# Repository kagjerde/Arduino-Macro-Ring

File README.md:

# Arduino-Macro-Ring

This project is for a RGB LED ring for macro photography or microscopes, to reduce shadows and reflections in the image.

The LED’s are controlled by a rotary switch that selects between different modes of brightness, colour and number of LED’s lit.  
Modes:

0. Set brightness, default full brightness with white light
1. Set Colour
- White
- Warm white
- Cool white
- Blue
- Red
- Green
- Random
2. Set number of LED's
3. Rotate number of LED's
4. Two opposite LED's
5. Four opposite LED's

## Hardware

- The project contains 3D model for a small enclosure for the electronics, and an arm intended for mounting on a microscope.
- It uses a WS2812B Module Strip from [Aliexpress](https://www.aliexpress.com/item/WS2812B-Module-Strip-24-Bits-24-X-WS2812-5050-RGB-LED-Ring-Lamp-Light-with-Integrated/32842513885.html?spm=a2g0s.9042311.0.0.27424c4dtHlEIW)
- The LED strip is controlled using a Arduino Nano microcontroller. 
- The mode selection is shown on a 7-segment display.

## Software

The software is written in C and relies on the Adafruit NeoPixel library.
New modes of operation can easily be added to the program.

## Circuit diagram

## Licence

2019 MIT

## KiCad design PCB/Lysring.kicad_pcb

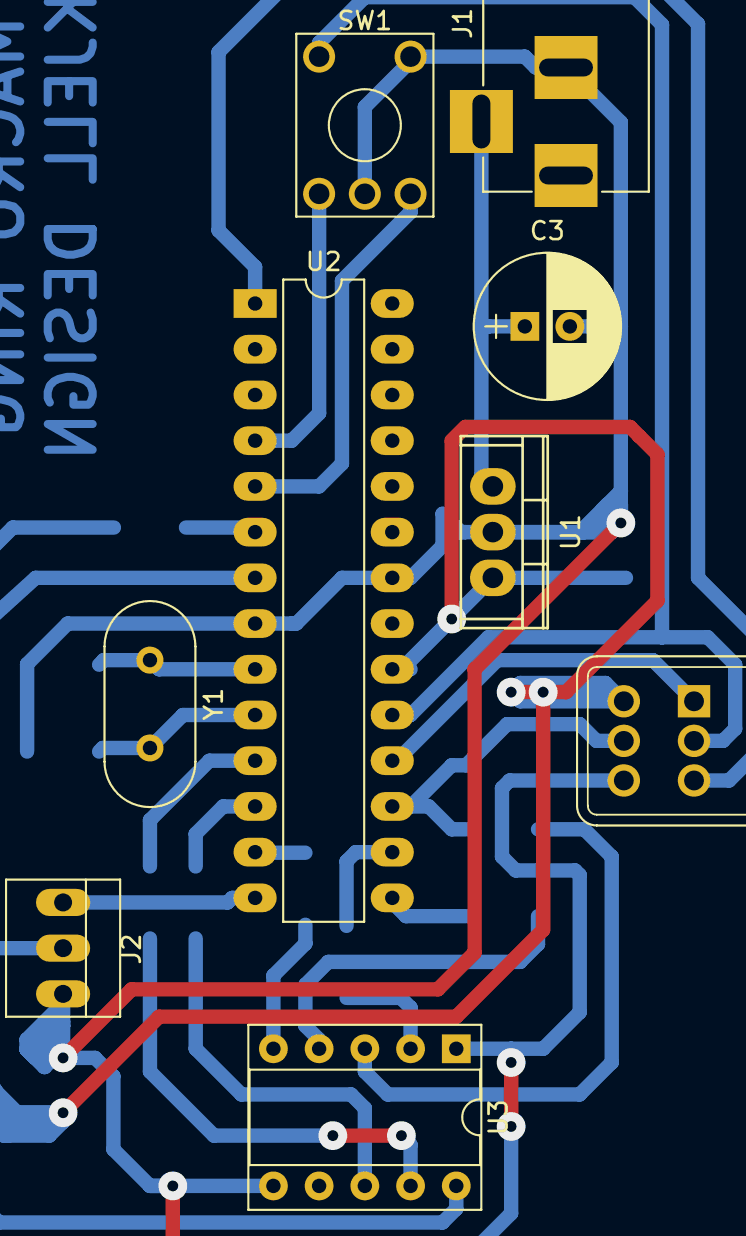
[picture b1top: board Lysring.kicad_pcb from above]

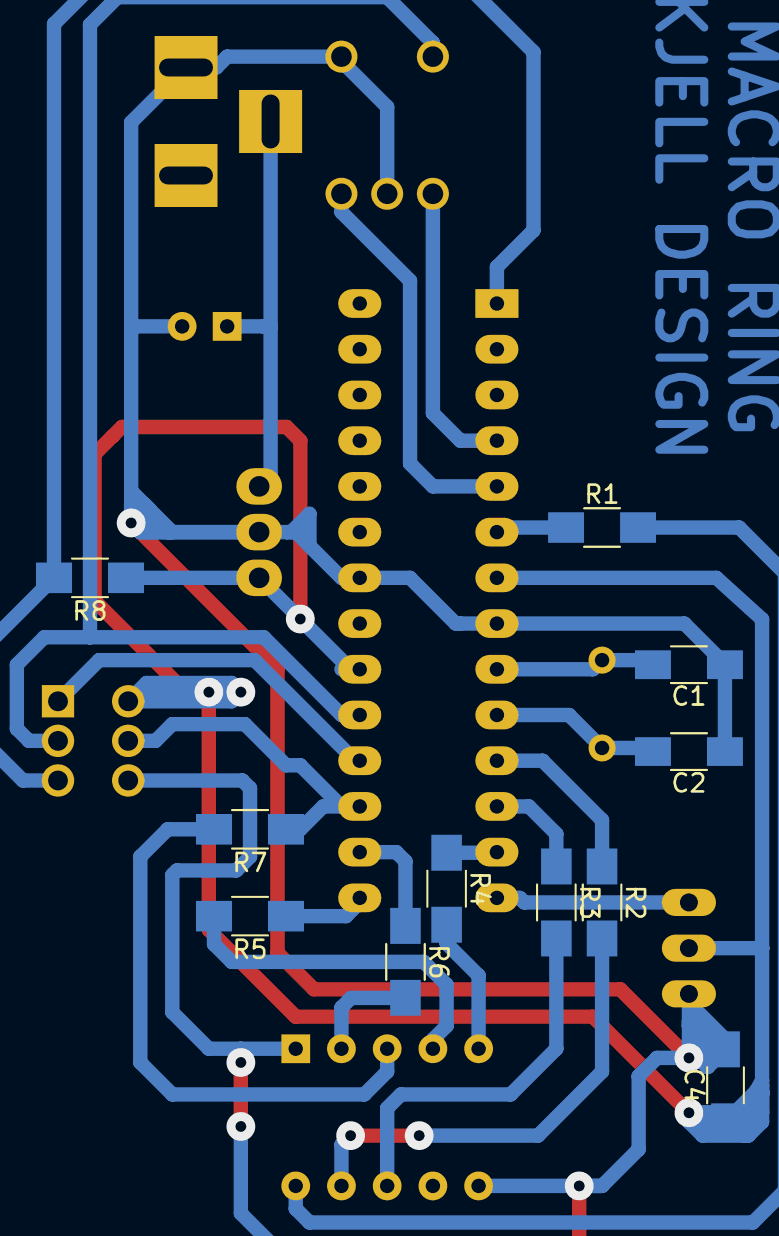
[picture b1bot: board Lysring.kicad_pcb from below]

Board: 2 copper layers, 20 parts (11 on the bottom side), 25 nets.

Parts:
C1, C2: C_Small; C_1206_HandSoldering
C3: CP; CP_Radial_D8.0mm_P2.50mm
C4: C; C_1206_HandSoldering
J1: Barrel_Jack; BARREL_JACK
J2: Conn_01x03; PINHEAD1-3
J3: Conn_02x03_Odd_Even; B06-J11DK_2x03_Pitch2.54mm
R1, R2, R3, R4, R5, R6, R7, R8: R; R_1206_HandSoldering
SW1: Rotary_Encoder_Switch; KSA_Tactile_SPST
U1: L7805; TO-220
U2: ATMEGA328P-PU; DIP-28_W7.62mm_LongPads
U3: 7SEGMENT_CC; DIP-10_W7.62mm_Socket
Y1: Crystal_Small; Crystal_HC49-4H_Vertical

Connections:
/VCC: C4.1, J2.2, J3.2, R8.1, U1.3, U2.7, U2.20
GND: C1.1, C2.1, C3.2, C4.2, J1.2, J2.3, J3.6, SW1.2, SW1.5, U1.2, U2.8, U2.22, U3.1, U3.6
unnamed: C1.2, U2.9, Y1.1
unnamed: C2.2, U2.10, Y1.2
unnamed: C3.1, J1.3, U1.1
unnamed: J2.1, U2.14
unnamed: J3.1, U2.18
unnamed: J3.3, SW1.4, U2.19
unnamed: J3.4, R7.1, U2.17
unnamed: J3.5, R8.2, U2.1
unnamed: R1.1, U2.6
unnamed: R1.2, U3.10
unnamed: R2.1, U2.11
unnamed: R2.2, U3.9
unnamed: R3.1, U2.12
unnamed: R3.2, U3.8
unnamed: R4.1, U2.13
unnamed: R4.2, U3.5
unnamed: R5.1, U2.15
unnamed: R5.2, U3.4
unnamed: R6.1, U2.16
unnamed: R6.2, U3.2
unnamed: R7.2, U3.3
unnamed: SW1.1, U2.4
unnamed: SW1.3, U2.5
